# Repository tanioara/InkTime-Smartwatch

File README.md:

## System Overview

InkTime is a low-power wearable platform built around the nRF52840 SoC, integrating MCU functionality with BLE connectivity.

System power is regulated via an RT6160 buck-boost converter, maintaining a stable 3.3V rail across the full Li-Po discharge range.

---

## Functional Architecture

The system is partitioned into three main domains:

- **Compute & RF** – nRF52840 (processing + BLE stack)
- **Power Management (PMIC + Regulation)** – charging and DC-DC conversion
- **Peripheral Interfaces** – sensors, display, and user I/O

### Block Diagram

---

## Hardware Overview

### Processing Core
nRF52840:
- ARM Cortex-M4F @ 64 MHz  
- Integrated BLE 5.x stack  
- EasyDMA for peripheral offloading  

Enables low-duty-cycle operation with minimal CPU wake time.

---

### Power Subsystem

- **Charging (BQ25180):**  
  Linear charger with CC/CV profile and I2C control. Supports ship mode for ultra-low leakage.

- **Regulation (RT6160):**  
  Buck-boost topology ensures a regulated 3.3V system rail independent of battery voltage (≈3.0–4.2V range).  
  Eliminates brown-out conditions during RF TX bursts.

---

### Interfaces & Peripherals

- **SPI (Display):**  
  Dedicated bus for E-Paper panel. Power is only consumed during refresh cycles (bi-stable behavior).

- **I2C (Sensors / PMIC):**  
  Shared bus for IMU and power IC.  
  BMA423 operates in interrupt mode → event-driven MCU wake-up.

---

## Bill of Materials

| Ref | Device | Function | Package | JLC | Datasheet |
| :-- | :-- | :-- | :-- | :-- | :-- |
| U1 | nRF52840 | MCU + BLE radio | QFN-48 | C3606653 | https://www.lcsc.com/datasheet/C3606653.pdf |
| IC9 | RT6160 | Buck-boost regulator (3.3V rail) | WLCSP-15B | C7065276 | https://wmsc.lcsc.com/wmsc/upload/file/pdf/v2/lcsc/2312271436_Richtek-Tech-RT6160AWSC_C7065276.pdf |
| IC1 | BQ25180 | Li-Po charger / PMIC | DSBGA-8 | C3682423 | https://www.ti.com/cn/lit/ds/symlink/bq25180.pdf?ts=1775594237116 |
| U2 | MAX17048G | Battery fuel gauge (I2C) | DFN-8-EP | C2682616 | https://www.lcsc.com/datasheet/lcsc_datasheet_2410121738_Analog-Devices-Inc--Maxim-Integrated-MAX17048G-T10_C2682616.pdf |
| IC3 | BMA423 | 3-axis accelerometer | LGA-12 | C189517 | https://www.lcsc.com/datasheet/C189517.pdf |
| IC2 | DRV2605 | Haptic driver | DSBGA-9 | C81079 | https://www.ti.com/cn/lit/gpn/drv2605 |
| ANT1 | 2.45GHz antenna | RF interface (BLE) | 1206 | C2917717 | https://www.lcsc.com/datasheet/lcsc_datasheet_2404021210_Johanson-Dielectrics-2450AT18B100E_C2917717.pdf |
| X1 | 32 MHz crystal | HF clock source | SMD3225 | C9009 | https://www.lcsc.com/datasheet/lcsc_datasheet_2403291504_YXC-Crystal-Oscillators-X322532MOB4SI_C9009.pdf |
| X2 | 32.768 kHz crystal | LF RTC clock | SMD3215 | C32346 | https://www.lcsc.com/datasheet/lcsc_datasheet_2404180925_Seiko-Epson-Q13FC13500004_C32346.pdf |
| J4 | USB-C | Power + data interface | SMD | C709357 | https://www.lcsc.com/datasheet/lcsc_datasheet_2404191039_Shenzhen-Kinghelm-Elec-KH-TYPE-C-16P_C709357.pdf |
| J1 | FPC (24p) | Display interface | 0.5mm | C122434 | https://www.molex.com/content/dam/molex/molex-dot-com/products/automated/en-us/salesdrawingpdf/503/503480/5034802400_sd.pdf |
| J2 | FFC (6p) | Auxiliary connector | 1mm | C90533 | https://wmsc.lcsc.com/wmsc/upload/file/pdf/v2/lcsc/1810141506_LX-FFC6P1-0mm7CM_C90533.pdf |
| Q1 | IRF4905PBF | P-MOS high-side switch | TO-220AB | C2564 | https://www.lcsc.com/datasheet/lcsc_datasheet_1809041724_Infineon-Technologies-IRF4905PBF_C2564.pdf |
| Q3 | Si1308EDL | N-MOS load switch | SOT-323 | C469327 | https://www.lcsc.com/datasheet/lcsc_datasheet_1912202016_Vishay-Intertech-SI1308EDL-T1-GE3_C469327.pdf |
| D3 | USBLC6-2SC6Y | USB ESD protection | SOT-23-6L | C2969755 | https://wmsc.lcsc.com/wmsc/upload/file/pdf/v2/lcsc/2211080730_STMicroelectronics-USBLC6-2SC6Y_C2969755.pdf |
| D2, D4, D5 | MBR0530 | Schottky diodes | SOD-123 | C82046 | https://www.lcsc.com/datasheet/lcsc_datasheet_2304140030_onsemi-MBR0530T1G_C82046.pdf |
| L5 | 4.7µH | DC-DC inductor | 4.8×4.8 | C1329646 | https://wmsc.lcsc.com/wmsc/upload/file/pdf/v2/lcsc/2304140030_BOURNS-SRR4828A-4R7Y_C1329646.pdf |
| L7 | 470nH | Filtering inductor | 1008 | C5832368 | https://wmsc.lcsc.com/wmsc/upload/file/pdf/v2/lcsc/2306021632_cjiang--Changjiang-Microelectronics-Tech-FTC252012SR47MBCA_C5832368.pdf |
| L1–L3 | 27nH | RF matching network | 0402 | C12669 | https://www.lcsc.com/datasheet/lcsc_datasheet_2304140030_Murata-Electronics-LQG15HS27NJ02D_C12669.pdf |
| SW_* | Tactile switches | User input | SMD | C569760 | https://wmsc.lcsc.com/wmsc/upload/file/pdf/v2/lcsc/2301111010_PANASONIC-EVPAKE31A_C569760.pdf |
| R* | 7.68kΩ | Bias / pull-ups | 0201 | C3920633 | https://wmsc.lcsc.com/wmsc/upload/file/pdf/v2/lcsc/2404081048_TE-Connectivity-CPF0201B511RE1_C3920633.pdf |
| C* | MLCC | Decoupling / bulk | 0201 | C9900156064 | https://ds.yuden.co.jp/TYCOMPAS/or/download?pn=MLAST063SCG681JFNA01&fileType=CA |
| TP | Test pads | Debug access | Copper | N/A | N/A |
| SJ1 | Solder jumper | Config link | Copper | N/A | N/A |

---

## MCU Pin Configuration

| Function | Signal | Pin | Dir | Notes |
| :-- | :-- | :-- | :-- | :-- |
| SPI (Display) | SCK | P1.01 | Out | Routed adjacent to FPC |
| SPI (Display) | MOSI | P1.02 | Out | Data line |
| SPI (Display) | CS | P1.03 | Out | Active low |
| Display Ctrl | D/C | P1.04 | Out | Command/data select |
| I2C | SDA | P0.26 | I/O | Shared bus |
| I2C | SCL | P0.27 | Out | Clock |
| IMU | INT1 | P0.11 | In | Wake interrupt |
| Button | BTN_UP | P0.13 | In | Internal pull-up |

---

## Design Notes

- **Pin muxing:** optimized for routing simplicity and minimal trace crossover  
- **System architecture:** event-driven (interrupt-based) → reduced average current  
- **PDN:** local decoupling placed <1mm from VDD pins  
- **RF layout:** strict antenna keep-out enforced (no copper below radiator)

---

## Images

### 3D PCB

### Assembly

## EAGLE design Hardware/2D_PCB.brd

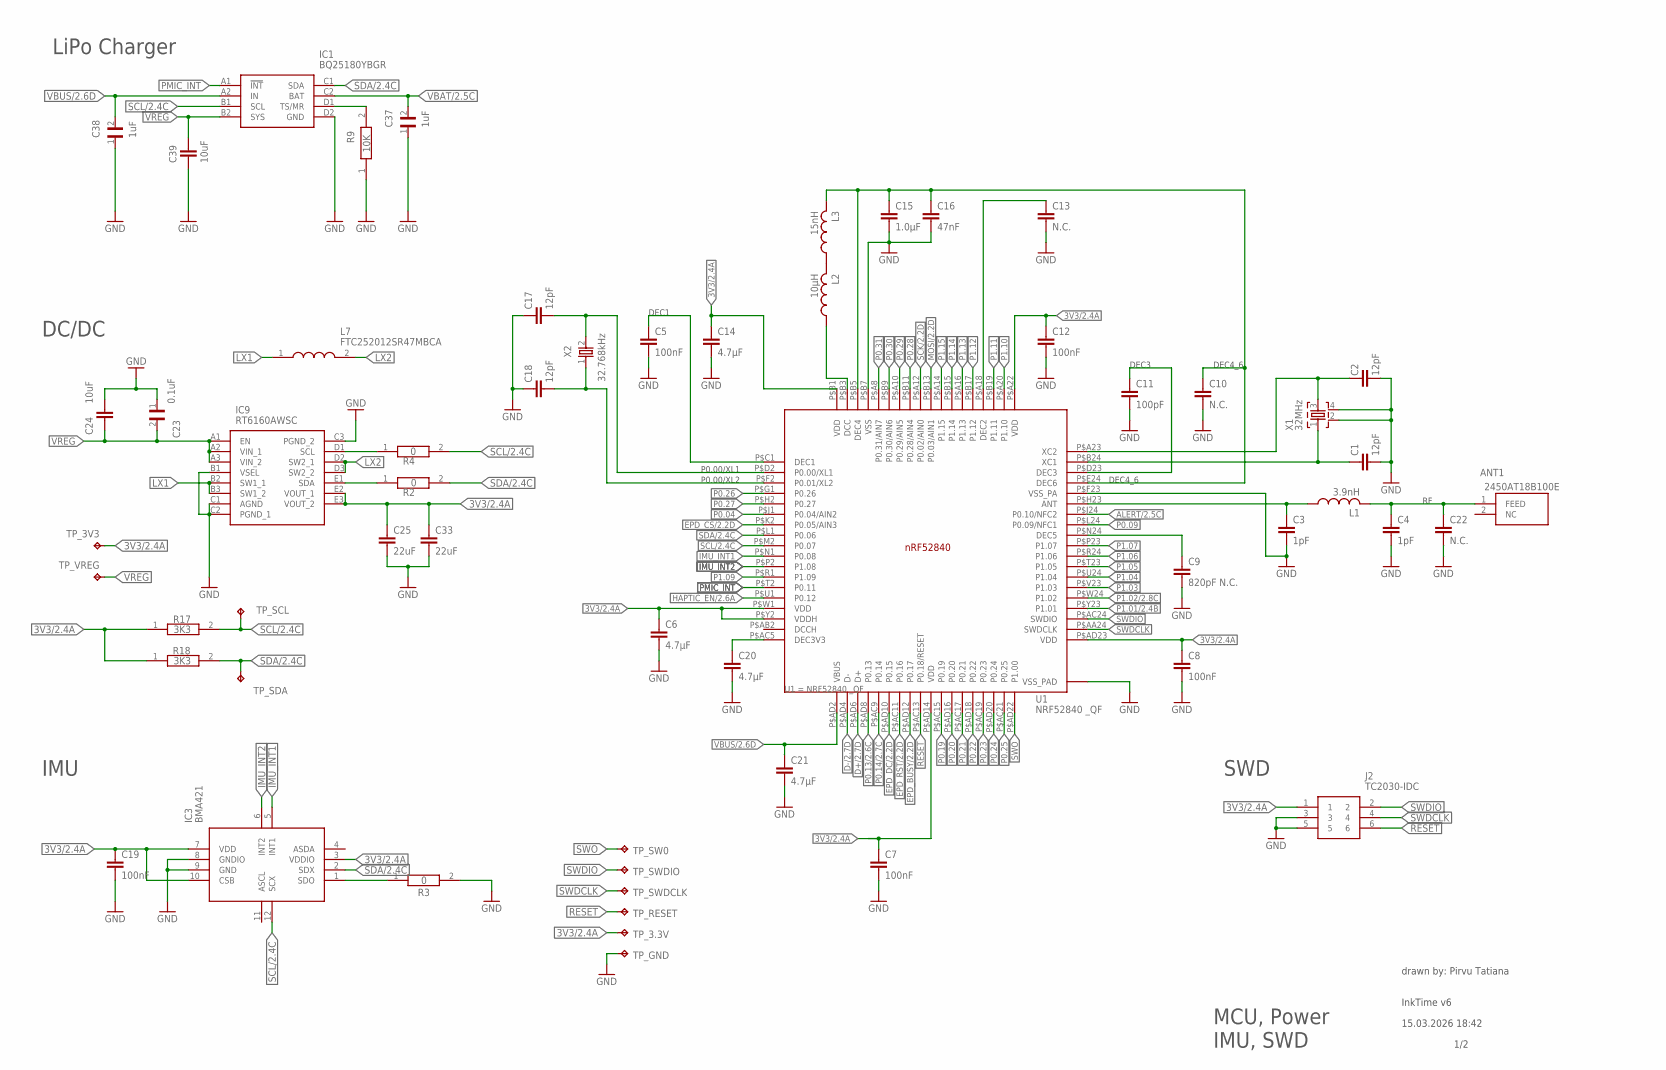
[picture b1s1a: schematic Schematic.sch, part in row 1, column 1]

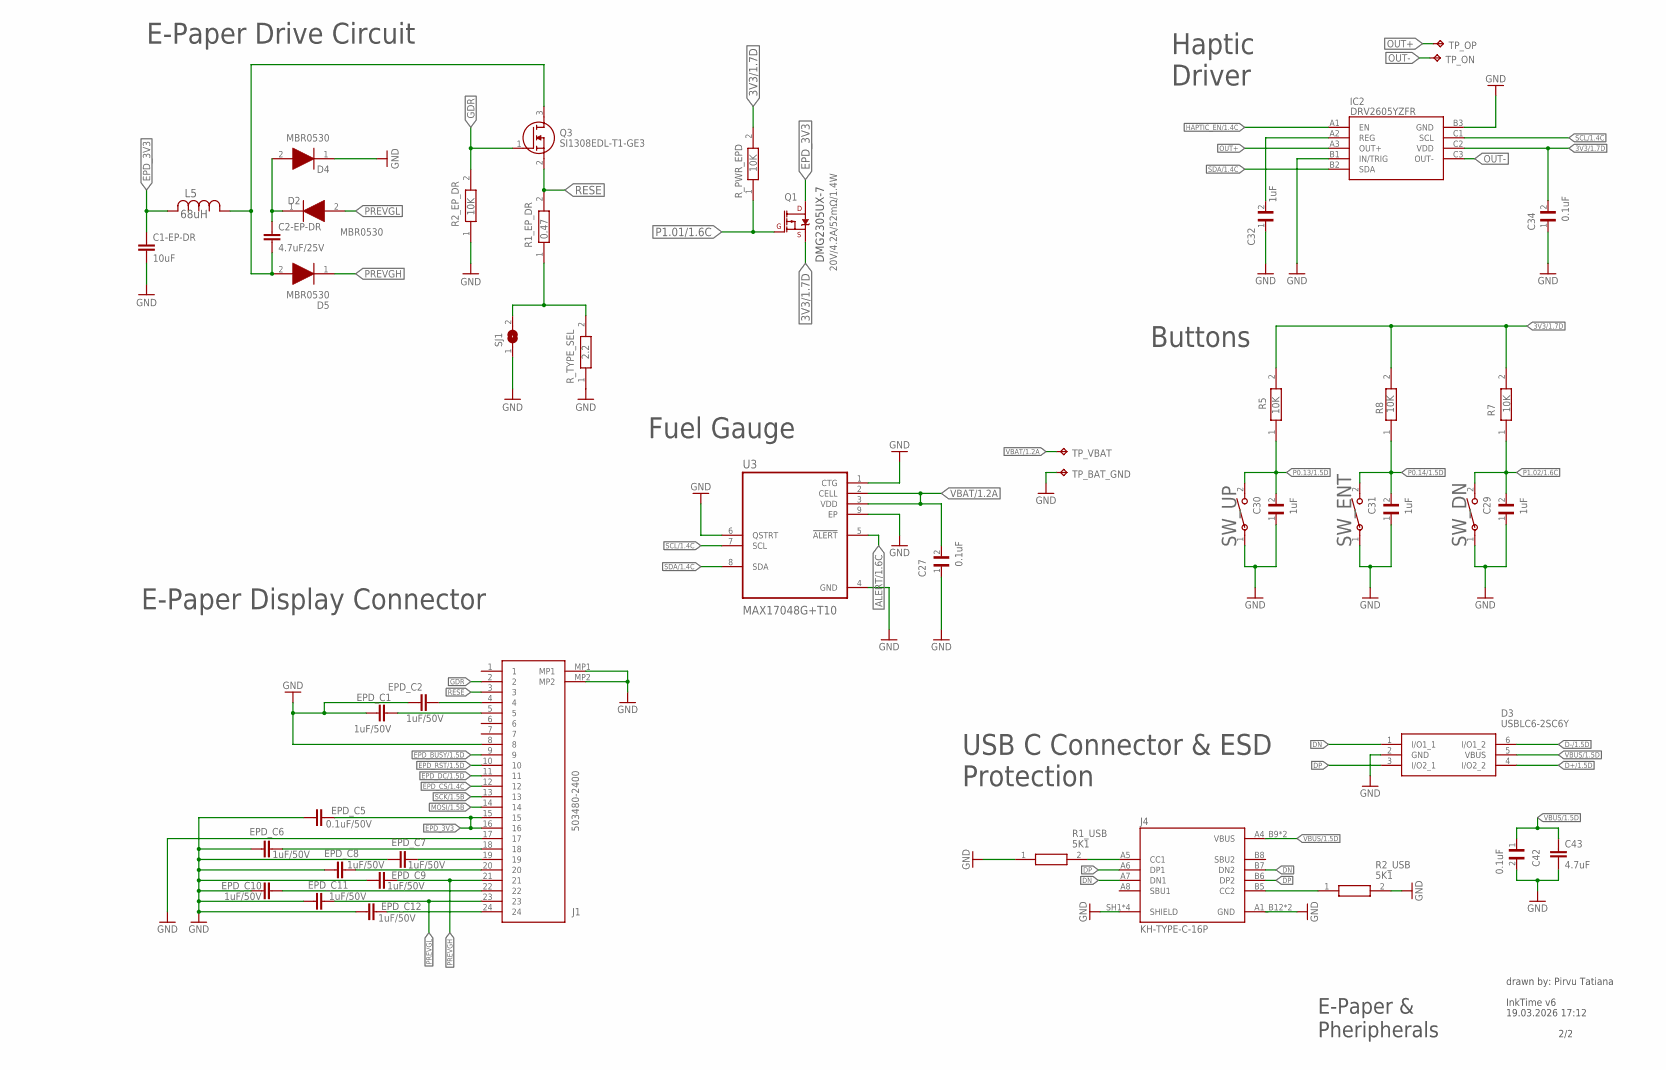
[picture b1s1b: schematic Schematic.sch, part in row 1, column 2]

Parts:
ANT1: 2450AT18B100E; 2450AT18B100E_ANTC3216X140N
C1, C2, C17, C18: 12pF; NORDIC_NRF_3_RESC0201_L
C1-EP-DR: 10uF; NORDIC_NRF_3_RESC0201_L
C2-EP-DR: 4.7uF/25V; NORDIC_NRF_3_RESC0201_L
C3, C4: 1pF; NORDIC_NRF_3_RESC0201_L
C5, C7, C8, C12, C19: 100nF; NORDIC_NRF_3_RESC0201_L
C6, C14, C20, C21: 4.7µF; NORDIC_NRF_3_RESC0201_L
C9: 820pF N.C.; NORDIC_NRF_3_RESC0201_L
C10, C13, C22: N.C.; NORDIC_NRF_3_RESC0201_L
C11: 100pF; NORDIC_NRF_3_RESC0201_L
C15: 1.0µF; NORDIC_NRF_3_RESC0201_L
C16: 47nF; NORDIC_NRF_3_RESC0201_L
C23, C27, C34, C42: 0.1uF; GRM011R60J152KE01L_2_CAPC0201X13N
C24, C39: 10uF; PERFECT_0402_0402
C25, C33: 22uF; PERFECT_0402_0402
C29, C30, C31, C32, C37, C38: 1uF; GRM011R60J152KE01L_2_CAPC0201X13N
C43: 4.7uF; NORDIC_NRF_3_RESC0201_L
D2, D4, D5: MBR0530; ESP32_C6_LIBRARY_5_SOD3716X135N
D3: USBLC6-2SC6Y; ESP32_C6_LIBRARY_3_SOT95P280X145-6N
EPD_C1, EPD_C2, EPD_C6, EPD_C7, EPD_C8, EPD_C9, EPD_C10, EPD_C11, EPD_C12: 1uF/50V; NORDIC_NRF_3_RESC0201_L
EPD_C5: 0.1uF/50V; NORDIC_NRF_3_RESC0201_L
IC1: BQ25180YBGR; BQ25180YBGR_BGA8C40P2X4_100X155X50
IC2: DRV2605YZFR; DRV2605YZFR_BGA9C50P3X3_144X144X62
IC3: BMA421; BMA423_BMA423
IC9: RT6160AWSC; RT6160AWSC_BGA15C40P3X5_140X230X60
J1: 503480-2400; 503480-2400_5034802400
J2: TC2030-IDC; TC2030-IDC_TC2030IDC
J4: KH-TYPE-C-16P; KH-TYPE-C-16P_KINGHELM_KH-TYPE-C-16P
L1: 3.9nH; NORDIC_NRF_2_RESC0402_L
L2: 10µH; NORDIC_NRF_2_RESC0402_L
L3: 15nH; NORDIC_NRF_2_RESC0402_L
L5: 68uH; ESP32_C6_LIBRARY_2_IND_4828-WE-TPC_WRE
L7: FTC252012SR47MBCA; MLP2016SR47MT0S1_INDC2016X100N
Q1: 20V/4.2A/52mΩ/1.4W; ESP32_C6_LIBRARY_4_ESP32_C6_LIBRARY_4_ESP32_C6_LIBRARY_4_ES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
Q3: SI1308EDL-T1-GE3; ESP32_C6_LIBRARY_6_SOT65P210X110-3N
R1_EP_DR: 0.47; CPF0201D7K68C1_0201
R1_USB, R2_USB: 5K1; ERA-1AEB3401C_0201
R2, R3, R4: 0; CPF0201D7K68C1_0201
R2_EP_DR, R9: 10K; CPF0201D7K68C1_0201
R5, R7, R8: 10K; ERA-1AEB3401C_0201
R17, R18: 3K3; CPF0201D7K68C1_0201
R_PWR_EPD: 10K; CPF0201D7K68C1_0201
R_TYPE_SEL: 2.2; CPF0201D7K68C1_0201
SJ1: ESP32_C6_LIBRARY_7_JUMPER_SJ
SW_DN: 2025-10-22_07-23-44_LIBRARY_EVP-AKE31ASW_EVP-AKE3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; 2025-10-22_07-23-44_LIBRARY_SW_EVP-AKE31A_PAN
SW_ENT: 2025-10-22_07-23-44_LIBRARY_EVP-AKE31ASW_EVP-AKE3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; 2025-10-22_07-23-44_LIBRARY_SW_EVP-AKE31A_PAN
SW_UP: 2025-10-22_07-23-44_LIBRARY_EVP-AKE31ASW_EVP-AKE3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; 2025-10-22_07-23-44_LIBRARY_SW_EVP-AKE31A_PAN
TP_3.3V, TP_3V3: HECTOR_WATCH_1_TPTP20R; HECTOR_WATCH_1_TP20R
TP_BAT_GND: HECTOR_WATCH_1_TPTP20R; HECTOR_WATCH_1_TP20R
TP_GND: HECTOR_WATCH_1_TPTP20R; HECTOR_WATCH_1_TP20R
TP_ON: HECTOR_WATCH_1_TPTP20R; HECTOR_WATCH_1_TP20R
TP_OP: HECTOR_WATCH_1_TPTP20R; HECTOR_WATCH_1_TP20R
TP_RESET: HECTOR_WATCH_1_TPTP20R; HECTOR_WATCH_1_TP20R
TP_SCL: HECTOR_WATCH_1_TPTP20R; HECTOR_WATCH_1_TP20R
TP_SDA: HECTOR_WATCH_1_TPTP20R; HECTOR_WATCH_1_TP20R
TP_SW0: HECTOR_WATCH_1_TPTP20R; HECTOR_WATCH_1_TP20R
TP_SWDCLK: HECTOR_WATCH_1_TPTP20R; HECTOR_WATCH_1_TP20R
TP_SWDIO: HECTOR_WATCH_1_TPTP20R; HECTOR_WATCH_1_TP20R
TP_VBAT: HECTOR_WATCH_1_TPTP20R; HECTOR_WATCH_1_TP20R
TP_VREG: HECTOR_WATCH_1_TPTP20R; HECTOR_WATCH_1_TP20R
U1: NRF52840 _QF; NORDIC_NRF_4_AQFN50P700X700X85_HS-74N
U3: MAX17048G+T10; ESP32_C6_LIBRARY_SON50P200X200X80-9N
X1: 32MHz; NORDIC_NRF_BT-XTAL_2016_N
X2: 32.768kHz; NORDIC_NRF_1_XTAL_3215_N

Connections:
3V3/1.7D: C34.2, IC2.C2 (VDD), Q1.2 (S), R5.2, R7.2, R8.2, R_PWR_EPD.2
3V3/2.4A: C6.1, C7.1, C8.1, C12.1, C14.1, C19.1, C25.1, C33.1, IC3.3 (VDDIO), IC3.7 (VDD), IC3.10 (CSB), IC9.E2 (VOUT_1), IC9.E3 (VOUT_2), J2.1, R17.1, R18.1, TP_3.3V.TP, TP_3V3.TP, U1.P$A22 (VDD), U1.P$AD14 (VDD), U1.P$AD23 (VDD), U1.P$B1 (VDD), U1.P$W1 (VDD), U1.P$Y2 (VDDH)
ALERT/1.6C: U3.5 (!ALERT)
ALERT/2.5C: U1.P$J24 (P0.10/NFC2)
D+/1.5D: D3.4 (I/O2_2)
D+/2.7D: U1.P$AD6 (D+)
D-/1.5D: D3.6 (I/O1_2)
D-/2.7D: U1.P$AD4 (D-)
DN: D3.1 (I/O1_1), J4.A7 (DN1), J4.B7 (DN2)
DP: D3.3 (I/O2_1), J4.A6 (DP1), J4.B6 (DP2)
EPD_3V3: C1-EP-DR.1, EPD_C5.2, J1.15, J1.16, L5.2, Q1.3 (D)
EPD_BUSY/1.5D: J1.9
EPD_BUSY/2.2D: U1.P$AD12 (P0.17)
EPD_CS/1.4C: J1.12
EPD_CS/2.2D: U1.P$K2 (P0.05/AIN3)
EPD_DC/1.5D: J1.11
EPD_DC/2.2D: U1.P$AD10 (P0.15)
EPD_RST/1.5D: J1.10
EPD_RST/2.2D: U1.P$AC11 (P0.16)
GDR: J1.2, Q3.1 (G), R2_EP_DR.2
GND: C1.2, C1-EP-DR.2, C2.1, C3.2, C4.2, C5.2, C6.2, C7.2, C8.2, C9.2, C10.2, C11.2, C12.2, C13.2, C14.2, C15.2, C16.2, C17.1, C18.1, C19.2, C20.2, C21.2, C22.2, C23.1, C24.1, C25.2, C27.1, C29.1, C30.1, C31.1, C32.1, C33.2, C34.1, C37.1, C38.1, C39.2, C42.2, C43.2, D3.2 (GND), D4.1 (K), EPD_C1.1, EPD_C2.1, EPD_C5.1, EPD_C6.1, EPD_C7.1, EPD_C8.1, EPD_C9.1, EPD_C10.1, EPD_C11.1, EPD_C12.1, IC1.D2 (GND), IC2.B1 (IN/TRIG), IC2.B3 (GND), IC3.8 (GNDIO), IC3.9 (GND), IC9.B1 (VSEL), IC9.C1 (AGND), IC9.C2 (PGND_1), IC9.C3 (PGND_2), J1.8, J1.17, J1.MP1, J1.MP2, J2.3, J2.5, J4.A1_B12 (GND), J4.A12_B1 (GND), J4.SH1 (SHIELD), J4.SH2 (SHIELD), J4.SH3 (SHIELD), J4.SH4 (SHIELD), R1_USB.1, R2_EP_DR.1, R2_USB.2, R3.2, R9.1, R_TYPE_SEL.1, SJ1.1, SW_DN.1, SW_ENT.1, SW_UP.1, TP_BAT_GND.TP, TP_GND.TP, U1.P$74 (VSS_PAD), U1.P$75 (VSS_PAD), U1.P$76 (VSS_PAD), U1.P$77 (VSS_PAD), U1.P$78 (VSS_PAD), U1.P$79 (VSS_PAD), U1.P$80 (VSS_PAD), U1.P$81 (VSS_PAD), U1.P$82 (VSS_PAD), U1.P$83 (VSS_PAD), U1.P$84 (VSS_PAD), U1.P$85 (VSS_PAD), U1.P$86 (VSS_PAD), U1.P$87 (VSS_PAD), U1.P$88 (VSS_PAD), U1.P$89 (VSS_PAD), U1.P$90 (VSS_PAD), U1.P$B7 (VSS), U1.P$F23 (VSS_PA), U3.1 (CTG), U3.4 (GND), U3.6 (QSTRT), U3.9 (EP), X1.2, X1.4
HAPTIC_EN/1.4C: IC2.A1 (EN)
HAPTIC_EN/2.6A: U1.P$U1 (P0.12)
IMU_INT1: IC3.5 (INT1), U1.P$N1 (P0.08)
IMU_INT2: IC3.6 (INT2), U1.P$P2 (P1.08)
LX1: IC9.B2 (SW1_1), IC9.B3 (SW1_2), L7.1
LX2: L7.2
MOSI/1.5B: J1.14
MOSI/2.2D: U1.P$B13 (P0.03/AIN1)
unnamed: IC1.D1 (TS/MR), R9.2
unnamed: L2.1, U1.P$B3 (DCC)
unnamed: IC3.1 (SDO), R3.1
unnamed: L2.2, L3.1
unnamed: C10.1, C15.1, C16.1, L3.2, U1.P$B5 (DEC4), U1.P$E24 (DEC6)
unnamed: C13.1, U1.P$A18 (DEC2)
unnamed: C5.1, U1.P$C1 (DEC1)
unnamed: IC9.E1 (SDA), R2.1
unnamed: C17.2, U1.P$D2 (P0.00/XL1), X2.2
unnamed: IC9.D2 (SW2_1), IC9.D3 (SW2_2)
unnamed: IC9.D1 (SCL), R4.1
unnamed: C18.2, U1.P$F2 (P0.01/XL2), X2.1
unnamed: C20.1, U1.P$AC5 (DEC3V3)
unnamed: C9.1, U1.P$N24 (DEC5)
unnamed: C3.1, L1.1, U1.P$H23 (ANT)
unnamed: ANT1.1 (FEED), C4.1, C22.1, L1.2
unnamed: C11.1, U1.P$D23 (DEC3)
unnamed: C1.1, U1.P$B24 (XC1), X1.1
unnamed: C2.2, U1.P$A23 (XC2), X1.3
unnamed: C2-EP-DR.1, D2.1 (K), D4.2 (A)
unnamed: C2-EP-DR.2, D5.2 (A), L5.1, Q3.3 (D)
unnamed: R1_EP_DR.1, R_TYPE_SEL.2, SJ1.2
unnamed: C32.2, IC2.A2 (REG)
unnamed: J4.A5 (CC1), R1_USB.2
unnamed: J4.B5 (CC2), R2_USB.1
unnamed: EPD_C2.2, J1.4
unnamed: EPD_C1.2, J1.5
unnamed: EPD_C6.2, J1.18
unnamed: EPD_C7.2, J1.19
unnamed: EPD_C8.2, J1.20
unnamed: EPD_C10.2, J1.22
unnamed: EPD_C12.2, J1.24
OUT+: IC2.A3 (OUT+), TP_OP.TP
OUT-: IC2.C3 (OUT-), TP_ON.TP
P0.04: U1.P$J1 (P0.04/AIN2)
P0.09: U1.P$L24 (P0.09/NFC1)
P0.13/1.5D: C30.2, R5.1, SW_UP.2
P0.13/2.6C: U1.P$AD8 (P0.13)
P0.14/1.5D: C31.2, R8.1, SW_ENT.2
P0.14/2.7C: U1.P$AC9 (P0.14)
P0.19: U1.P$AC15 (P0.19)
P0.20: U1.P$AD16 (P0.20)
P0.21: U1.P$AC17 (P0.21)
P0.22: U1.P$AD18 (P0.22)
P0.23: U1.P$AC19 (P0.23)
P0.24: U1.P$AD20 (P0.24)
P0.25: U1.P$AC21 (P0.25)
P0.26: U1.P$G1 (P0.26)
P0.27: U1.P$H2 (P0.27)
P0.28: U1.P$B11 (P0.28/AIN4)
P0.29: U1.P$A10 (P0.29/AIN5)
P0.30: U1.P$B9 (P0.30/AIN6)
P0.31: U1.P$A8 (P0.31/AIN7)
P1.01/1.6C: Q1.1 (G), R_PWR_EPD.1
P1.01/2.4B: U1.P$Y23 (P1.01)
P1.02/1.6C: C29.2, R7.1, SW_DN.2
P1.02/2.8C: U1.P$W24 (P1.02)
P1.03: U1.P$V23 (P1.03)
P1.04: U1.P$U24 (P1.04)
P1.05: U1.P$T23 (P1.05)
P1.06: U1.P$R24 (P1.06)
P1.07: U1.P$P23 (P1.07)
P1.09: U1.P$R1 (P1.09)
P1.10: U1.P$A20 (P1.10)
P1.11: U1.P$B19 (P1.11)
P1.12: U1.P$B17 (P1.12)
P1.13: U1.P$A16 (P1.13)
P1.14: U1.P$B15 (P1.14)
P1.15: U1.P$A14 (P1.15)
PMIC_INT: IC1.A1 (!INT), U1.P$T2 (P0.11)
PREVGH: EPD_C9.2, J1.21
PREVGL: D2.2 (A), EPD_C11.2, J1.23
RESE: J1.3, Q3.2 (S), R1_EP_DR.2
RESET: J2.6, TP_RESET.TP, U1.P$AC13 (P0.18/RESET)
SCK/1.5B: J1.13
SCK/2.2D: U1.P$A12 (P0.02/AIN0)
SCL/1.4C: IC2.C1 (SCL), U3.7 (SCL)
SCL/2.4C: IC1.B1 (SCL), IC3.12 (SCX), R4.2, R17.2, TP_SCL.TP, U1.P$M2 (P0.07)
SDA/1.4C: IC2.B2 (SDA), U3.8 (SDA)
SDA/2.4C: IC1.C1 (SDA), IC3.2 (SDX), R2.2, R18.2, TP_SDA.TP, U1.P$L1 (P0.06)
SWDCLK: J2.4, TP_SWDCLK.TP, U1.P$AA24 (SWDCLK)
SWDIO: J2.2, TP_SWDIO.TP, U1.P$AC24 (SWDIO)
SWO: TP_SW0.TP, U1.P$AD22 (P1.00)
VBAT/1.2A: C27.2, TP_VBAT.TP, U3.2 (CELL), U3.3 (VDD)
VBAT/2.5C: C37.2, IC1.C2 (BAT)
VBUS/1.5D: C42.1, C43.1, D3.5 (VBUS), J4.A4_B9 (VBUS), J4.A9_B4 (VBUS)
VBUS/2.6D: C21.1, C38.2, IC1.A2 (IN), U1.P$AD2 (VBUS)
VREG: C23.2, C24.2, C39.1, IC1.B2 (SYS), IC9.A1 (EN), IC9.A2 (VIN_1), IC9.A3 (VIN_2), TP_VREG.TP

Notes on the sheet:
LiPo Charger
DC/DC
IMU
SWD
MCU, Power IMU, SWD
drawn by: Pirvu Tatiana
InkTime v6
15.03.2026 18:42
1/2
DEC1
P0.00/XL1
P0.00/XL2
DEC3
DEC4_6
E-Paper & Pheripherals
drawn by: Pirvu Tatiana
19.03.2026 17:12
2/2
Haptic Driver
Buttons
USB C Connector & ESD Protection
E-Paper Display Connector
Fuel Gauge
E-Paper Drive Circuit
DMG2305UX-7

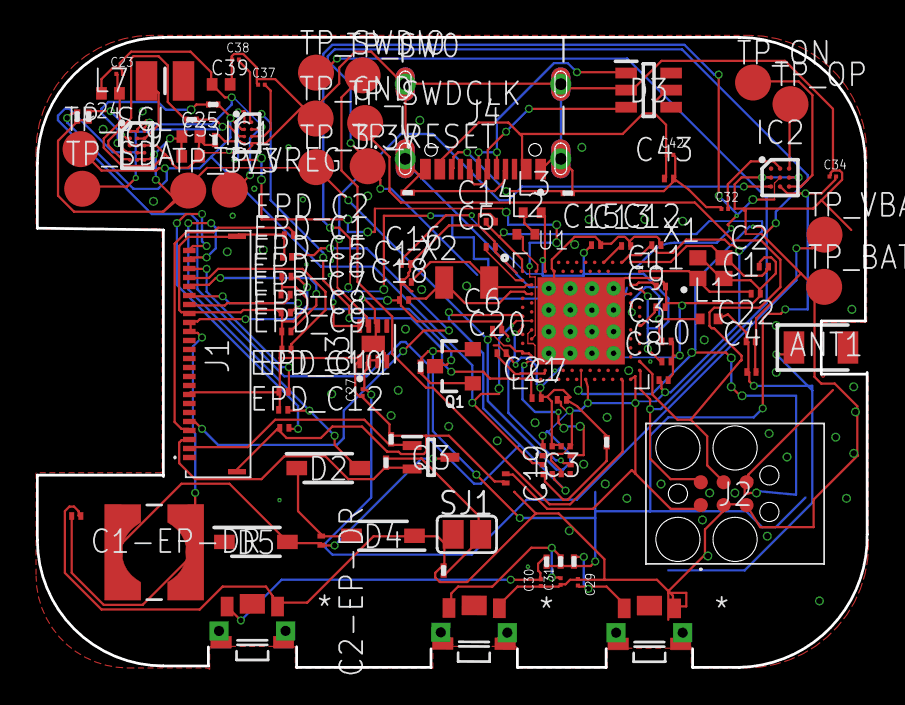
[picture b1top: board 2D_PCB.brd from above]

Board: 2 copper layers, 46.1 x 35.0 mm, 105 parts (0 on the bottom side), 65 nets.

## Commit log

2026-04-10 Add initial README with project title and author
2026-04-10 Added License
2026-04-10 Further changes
2026-04-18 am actualizat proiectul
2026-04-20 README
2026-04-20 Added diagram
2026-04-20 README updates

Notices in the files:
parts and their libraries:
COPYRIGHT: Copyright (C) 2024 Ultra Librarian. All rights reserved.
COPYRIGHT: Copyright (C) 2025 Ultra Librarian. All rights reserved.
